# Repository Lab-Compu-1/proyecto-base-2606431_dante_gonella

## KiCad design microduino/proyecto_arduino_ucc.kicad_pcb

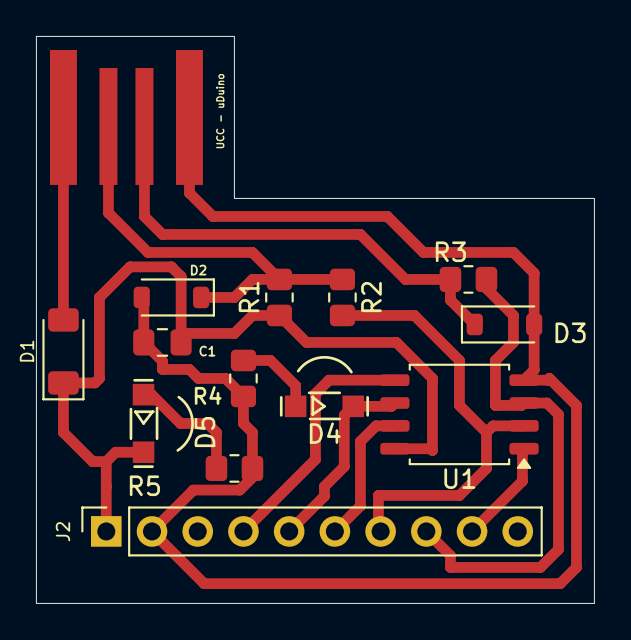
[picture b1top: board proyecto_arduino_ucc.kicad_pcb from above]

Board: 2 copper layers, 31.0 x 31.5 mm, 14 parts (0 on the bottom side), 12 nets.

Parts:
C1: C; C_0805_2012Metric_Pad1.18x1.45mm_HandSolder
D1: D_Zener; D_MiniMELF
D2, D3: D_SOD-123
D4: LED GREEN; LED.R
D5: LED RED; LED.R
J1: USB_A; USB_A_UCC
J2: Header; PinSocket_1x10_P2.54mm_Vertical
R1: 1.5K 5% 1/8W; R_0805_2012Metric_Pad1.20x1.40mm_HandSolder
R2, R3: 68 5% 1/8W; R_0805_2012Metric_Pad1.20x1.40mm_HandSolder
R4, R5: 330 5% 1/8W; R_0805_2012Metric_Pad1.20x1.40mm_HandSolder
U1: ATtiny85-20S; SOIC-8_5.3x5.3mm_P1.27mm

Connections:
+1V5: C1.1, D1.1 (K), D5.2 (A), J2.1, R1.1, U1.8 (VCC)
GND: C1.2, D2.2 (A), D3.2 (A), J1.4 (GND), J2.2, R4.2, R5.1, U1.4 (GND)
unnamed: D1.2 (A), J1.1 (VBUS)
unnamed: D2.1 (K), D3.1 (K), J1.2 (D-), J1.3 (D+), R1.2, R2.1, R3.1
unnamed: D4.2 (A), J2.5, U1.6 (PB1)
unnamed: D4.1 (K), R4.1
unnamed: D5.1 (K), R5.2
unnamed: J2.4, U1.5 (AREF/PB0)
unnamed: J2.6, U1.7 (PB2)
unnamed: J2.7, R2.2, U1.2 (XTAL1/PB3)
unnamed: J2.8, R3.2, U1.3 (XTAL2/PB4)
unnamed: J2.9, U1.1 (~RESET/PB5)

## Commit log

2026-05-22 GitHub Classroom Feedback
2026-05-22 Setting up GitHub Classroom Feedback
2026-05-29 Mi primer commit y entrega de proyecto kicad
2026-06-09 Entrega html para profe Nico
